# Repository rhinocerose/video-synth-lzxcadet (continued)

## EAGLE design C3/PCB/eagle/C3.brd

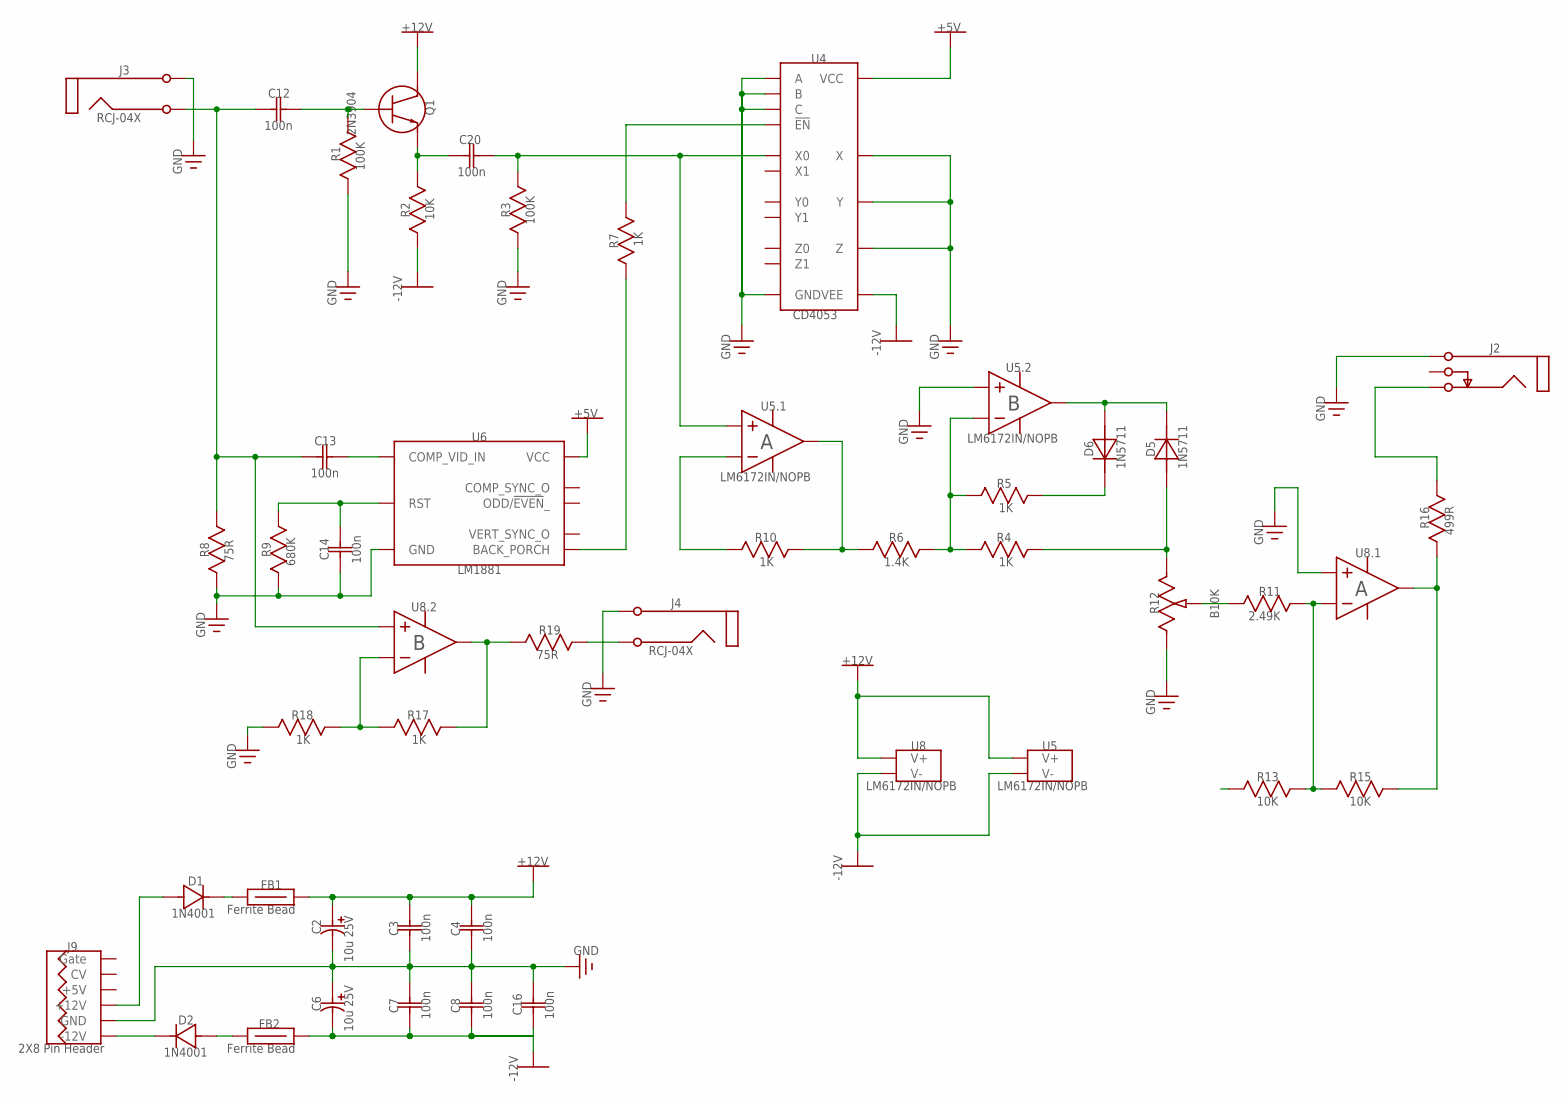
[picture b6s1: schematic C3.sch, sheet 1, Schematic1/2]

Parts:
C2, C6: 10u 25V; CAPPR-2/5.08
C3, C4, C7, C8, C12, C13, C14, C16, C20: 100n; CAP-2.54/6.6X3
D1, D2: 1N4001; DO-41
D5, D6: 1N5711; DO-35
FB1, FB2: 68R; FB-10.16/4.45X3.5
J2: PJ302M
J3: RCJ-04X
J4: RCJ-04X_23; RCJ-04X
J9: 2X8_PIN_HEADER; IDC16M
Q1: 2N3904; TO-92
R1, R3: 100K; RES-7.62/5.1X2.5
R2, R13, R15: 10K; RES-7.62/5.1X2.5
R4, R5, R7, R10, R17, R18: 1K; RES-7.62/5.1X2.5
R6: 1.4K; RES-7.62/5.1X2.5
R8, R19: 75R; RES-7.62/5.1X2.5
R9: 680K; RES-7.62/5.1X2.5
R11: 2.49K; RES-7.62/5.1X2.5
R12: B10K; ALPHA9H
R16: 499R; RES-7.62/5.1X2.5
U4: CD4053; DIP-16
U5, U8: LM6172IN/NOPB; DIP-8_16
U6: LM1881; DIP-8

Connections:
0V: C2.2 (MINUS), C3.2, C4.2, C6.1 (PLUS), C7.1, C8.1, C14.1, C16.1, J2.1A (Sleeve), J2.1B (Sleeve), J3.1 (Sleeve), J4.1 (Sleeve), J9.3 (GND), J9.4 (GND), J9.5 (GND), J9.6, J9.7, J9.8, R1.2 (B), R3.2 (B), R8.1 (A), R9.1 (A), R12.1 (CCW), R18.1 (A), U4.4 (Z), U4.8 (GND), U4.9 (C), U4.10 (B), U4.11 (A), U4.14 (X), U4.15 (Y), U5.5 (IN+), U6.4 (GND), U8.3 (IN+); also elsewhere on the board
+5V: U4.16 (VCC), U6.8 (VCC); also elsewhere on the board
+12V: C2.1 (PLUS), C3.1, C4.1, FB1.2, Q1.3 (C), U5.8 (V+), U8.8 (V+); also elsewhere on the board
-12V: C6.2 (MINUS), C7.2, C8.2, C16.2, FB2.2, R2.2 (B), U4.7 (VEE), U5.4 (V-), U8.4 (V-); also elsewhere on the board
BIAS_POT_OUT: R13.1 (A); also elsewhere on the board
Net_0: C20.2, Q1.1 (E), R2.1 (A)
Net_1: D2.2 (A), FB2.1
Net_2: D1.1 (K), FB1.1
Net_3: C20.1, R3.1 (A), U4.12 (X0), U5.3 (IN+)
Net_4: C13.2, U6.2 (COMP_VID_IN)
Net_5: D2.1 (K), J9.1 (-12V), J9.2 (-12V)
Net_6: R7.1 (A), U4.6 (!EN)
Net_7: R10.1 (A), U5.2 (IN-)
Net_8: J2.3A (Tip), J2.3B (Tip), R16.2 (B)
Net_9: R17.2 (B), R19.1 (A), U8.7 (OUT)
Net_10: R4.1 (A), R5.1 (A), R6.2 (B), U5.6 (IN-)
Net_11: D5.2 (A), R4.2 (B), R12.3 (CW)
Net_12: D6.1 (K), R5.2 (B)
Net_14: J9.11 (+5V), J9.12 (+5V)
Net_15: J9.13 (CV), J9.14 (CV)
Net_16: J9.15 (Gate), J9.16 (Gate)
Net_20: C12.1, Q1.2 (B), R1.1 (A)
Net_21: J2.2A (Switch), J2.2B (Switch)
Net_22: D5.1 (K), D6.2 (A), U5.7 (OUT)
Net_33: D1.2 (A), J9.9 (+12V), J9.10 (+12V)
Net_34: C12.2, C13.1, J3.2 (Tip), R8.2 (B), U8.5 (IN+)
Net_35: C14.2, R9.2 (B), U6.6 (RST)
Net_36: R7.2 (B), U6.5 (BACK_PORCH)
Net_37: R6.1 (A), R10.2 (B), U5.1 (OUT)
Net_38: R11.1 (A), R12.2 (W)
Net_39: R11.2 (B), R13.2 (B), R15.1 (A), U8.2 (IN-)
Net_40: R15.2 (B), R16.1 (A), U8.1 (OUT)
Net_42: R17.1 (A), R18.2 (B), U8.6 (IN-)
Net_43: J4.2 (Tip), R19.2 (B)

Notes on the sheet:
10u 25V
100n
C13
C14
1N4001
2N3904
RCJ-04X
100K
2X8 Pin Header
FB1
Ferrite Bead
FB2
C12
GND
+12V
-12V
+5V
75R
680K
LM1881
U5.1
LM6172IN/NOPB
10K
C20
CD4053
1N5711
1.4K
R12
B10K
U5.2
R10
U8.1
U8.2
R11
2.49K
R13
R15
R16
499R
R17

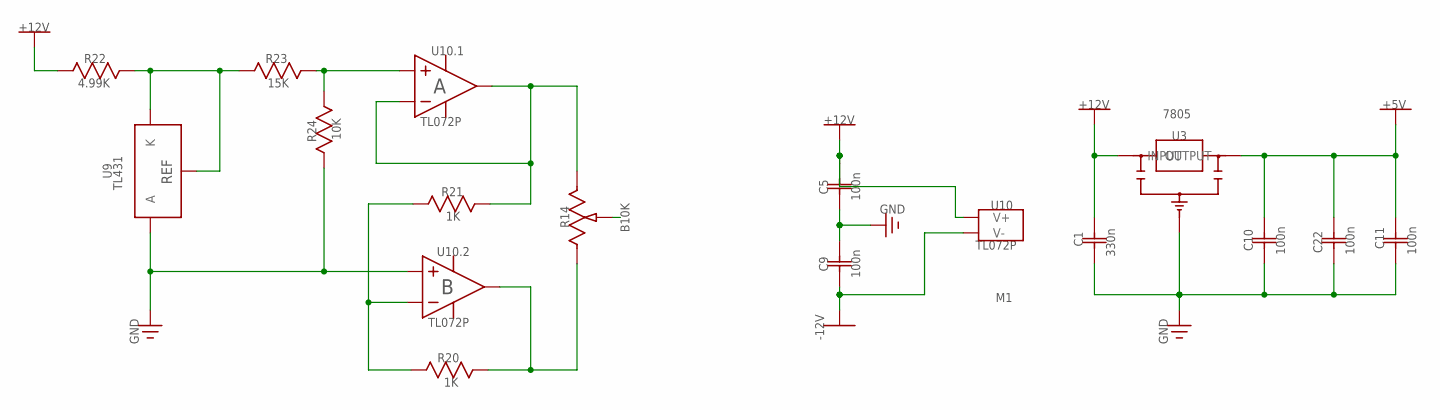
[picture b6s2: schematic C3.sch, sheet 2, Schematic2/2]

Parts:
C1: 330n; CAP-2.54/6.6X3
C5, C9, C10, C11, C22: 100n; CAP-2.54/6.6X3
M1: KEYSTONE621
R14: B10K; ALPHA9H
R20, R21: 1K; RES-7.62/5.1X2.5
R22: 4.99K; RES-7.62/5.1X2.5
R23: 15K; RES-7.62/5.1X2.5
R24: 10K; RES-7.62/5.1X2.5
U3: 7805; TO-220H
U9: TL431; TO-92-100R
U10: TL072P; DIP-8_16

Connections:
0V: C1.2, C5.2, C9.1, C10.2, C11.2, C22.2, R24.2 (B), U3.2 (GND), U9.2 (A), U10.5 (IN+); also elsewhere on the board
+5V: C10.1, C11.1, C22.1, U3.3 (OUTPUT); also elsewhere on the board
+12V: C1.1, C5.1, R22.2 (B), U3.1 (INPUT), U10.8 (V+); also elsewhere on the board
-12V: C9.2, U10.4 (V-); also elsewhere on the board
BIAS_POT_OUT: R14.2 (W); also elsewhere on the board
Net_13: R20.1 (A), R21.1 (A), U10.6 (IN-)
Net_17: R14.1 (CCW), R21.2 (B), U10.1 (OUT), U10.2 (IN-)
Net_18: R22.1 (A), R23.2 (B), U9.1 (K), U9.3 (REF)
Net_19: R14.3 (CW), R20.2 (B), U10.7 (OUT)
Net_30: R23.1 (A), R24.1 (A), U10.3 (IN+)

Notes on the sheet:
330n
C10
100n
C22
GND
+5V
7805
R14
B10K
+12V
R20
R21
R22
4.99K
R23
15K
R24
10K
REF
TL431
U10.1
TL072P
U10.2
U10
-12V
C11

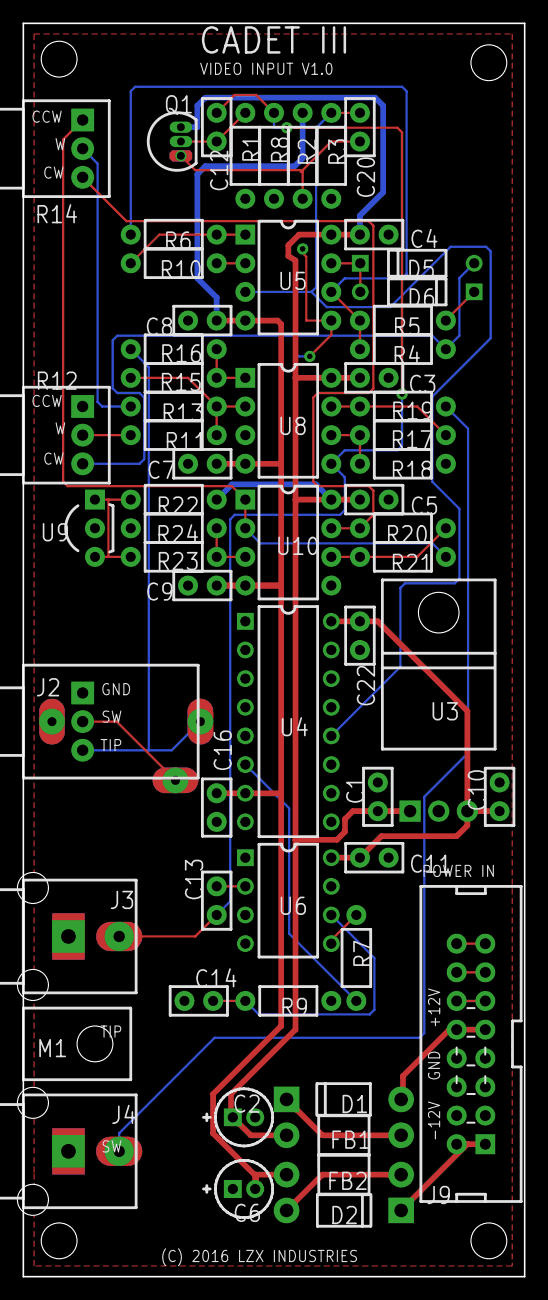
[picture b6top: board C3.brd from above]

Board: 2 copper layers, 44.5 x 111.1 mm, 60 parts (0 on the bottom side), 39 nets.

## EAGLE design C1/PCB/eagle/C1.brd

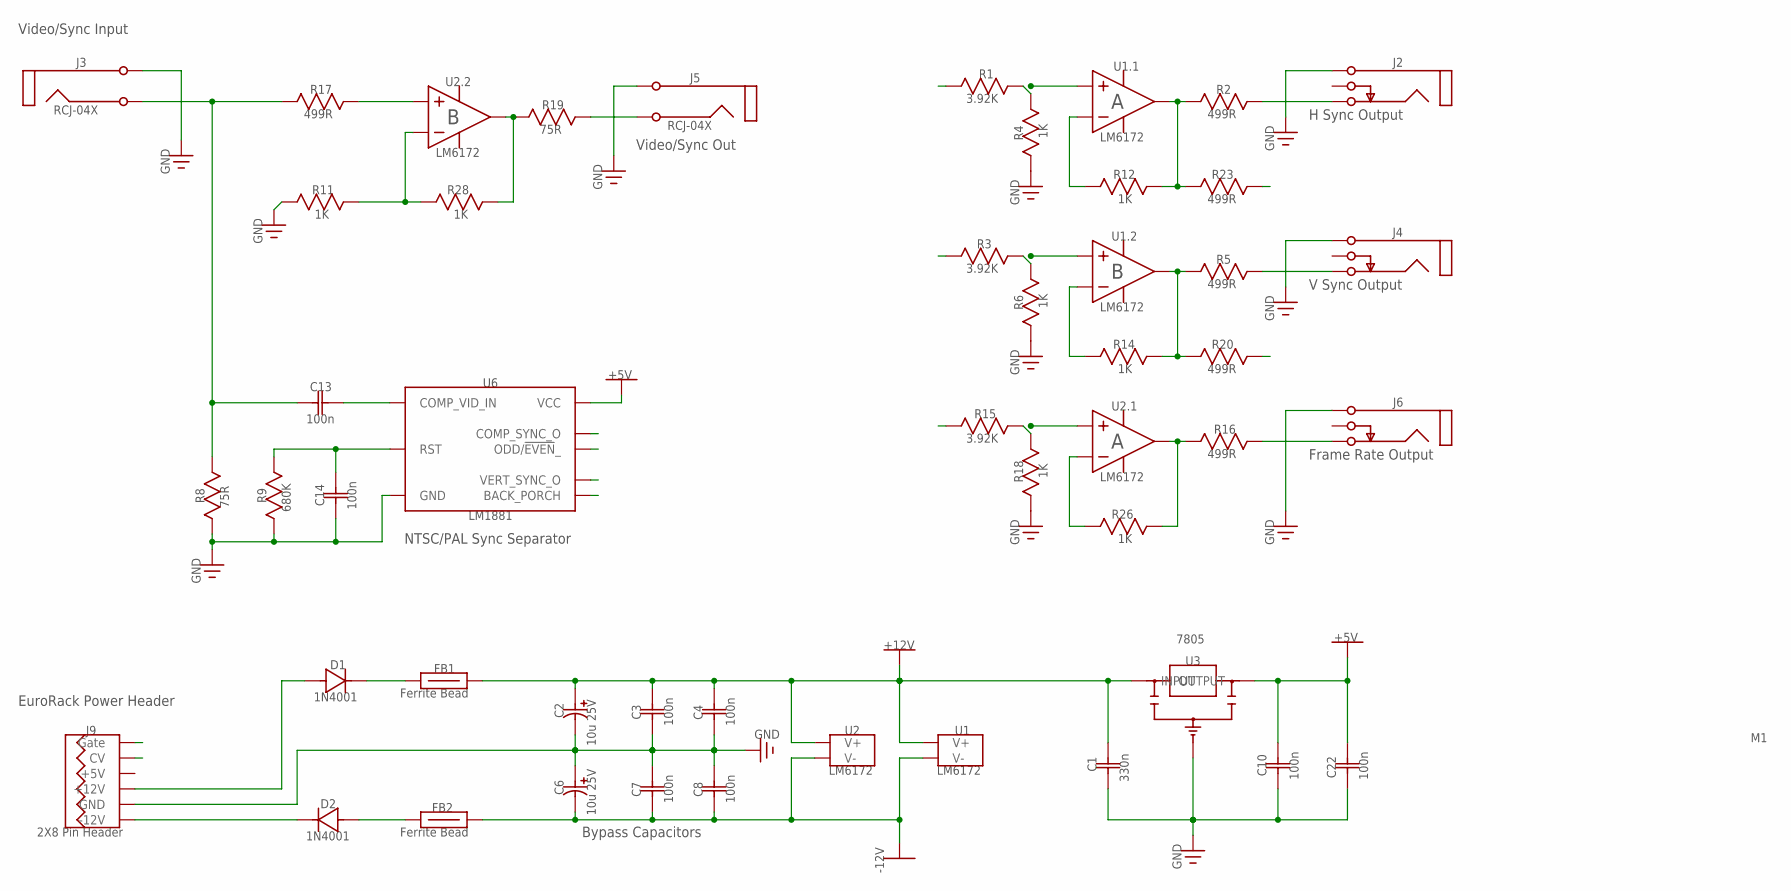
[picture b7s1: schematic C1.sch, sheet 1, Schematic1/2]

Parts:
C1: 330n; CAP-2.54/6.6X3
C2, C6: 10u 25V; CAPPR-2/5.08
C3, C4, C7, C8, C10, C13, C14, C22: 100n; CAP-2.54/6.6X3
D1, D2: 1N4001; DO-41
FB1, FB2: 68R; FB-10.16/4.45X3.5
J2, J4, J6: 3.5MM_JACK; PJ302M
J3: RCJ-04X
J5: RCJ-04X_23; RCJ-04X
J9: 2X8_PIN_HEADER; IDC16M
M1: KEYSTONE621
R1, R3, R15: 3.92K; RES-7.62/5.1X2.5
R2, R5, R16, R17, R20, R23: 499R; RES-7.62/5.1X2.5
R4, R6, R11, R12, R14, R18, R26, R28: 1K; RES-7.62/5.1X2.5
R8, R19: 75R; RES-7.62/5.1X2.5
R9: 680K; RES-7.62/5.1X2.5
U1, U2: LM6172; DIP-8
U3: 7805; TO-220H
U6: LM1881; DIP-8_12

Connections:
0V: C1.2, C2.2 (MINUS), C3.2, C4.2, C6.1 (PLUS), C7.1, C8.1, C10.2, C14.1, C22.2, J2.1A (Sleeve), J2.1B (Sleeve), J3.1 (Sleeve), J4.1A (Sleeve), J4.1B (Sleeve), J5.1 (Sleeve), J6.1A (Sleeve), J6.1B (Sleeve), J9.3 (GND), J9.4 (GND), J9.5 (GND), J9.6, J9.7, J9.8, R4.1 (A), R6.1 (A), R8.1 (A), R9.1 (A), R11.1 (A), R18.1 (A), U3.2 (GND), U6.4 (GND); also elsewhere on the board
+5V: C10.1, C22.1, U3.3 (OUTPUT), U6.8 (VCC); also elsewhere on the board
+12V: C1.1, C2.1 (PLUS), C3.1, C4.1, FB1.2, U1.8 (V+), U2.8 (V+), U3.1 (INPUT)
-12V: C6.2 (MINUS), C7.2, C8.2, FB2.2, U1.4 (V-), U2.4 (V-)
ATMEGA88_HSYNC_INV: R1.1 (A); also elsewhere on the board
ATMEGA88_ODDEVEN: R15.1 (A); also elsewhere on the board
ATMEGA88_VSYNC_INV: R3.1 (A); also elsewhere on the board
HSYNC_BUS_OUT: J9.13 (CV), J9.14 (CV), R23.2 (B)
LM1881_CSYNC: U6.1 (COMP_SYNC_O); also elsewhere on the board
LM1881_ODDEVEN: U6.7 (ODD/!EVEN!_); also elsewhere on the board
LM1881_VSYNC: U6.3 (VERT_SYNC_O); also elsewhere on the board
Net_0: J5.2 (Tip), R19.2 (B)
Net_1: D2.2 (A), FB2.1
Net_2: D1.1 (K), FB1.1
Net_3: R14.1 (A), U1.6 (IN-)
Net_4: C13.2, U6.2 (COMP_VID_IN)
Net_5: D2.1 (K), J9.1 (-12V), J9.2 (-12V)
Net_6: R3.2 (B), R6.2 (B), U1.5 (IN+)
Net_7: J4.3A (Tip), J4.3B (Tip), R5.2 (B)
Net_8: J2.2A (Switch), J2.2B (Switch)
Net_9: R1.2 (B), R4.2 (B), U1.3 (IN+)
Net_10: J9.11 (+5V), J9.12 (+5V)
Net_11: J2.3A (Tip), J2.3B (Tip), R2.2 (B)
Net_12: R5.1 (A), R14.2 (B), R20.1 (A), U1.7 (OUT)
Net_14: R11.2 (B), R28.1 (A), U2.6 (IN-)
Net_19: R15.2 (B), R18.2 (B), U2.3 (IN+)
Net_20: J6.3A (Tip), J6.3B (Tip), R16.2 (B)
Net_21: R26.1 (A), U2.2 (IN-)
Net_22: R16.1 (A), R26.2 (B), U2.1 (OUT)
Net_24: R17.2 (B), U2.5 (IN+)
Net_27: R19.1 (A), R28.2 (B), U2.7 (OUT)
Net_33: D1.2 (A), J9.9 (+12V), J9.10 (+12V)
Net_34: C13.1, J3.2 (Tip), R8.2 (B), R17.1 (A)
Net_35: C14.2, R9.2 (B), U6.6 (RST)
Net_52: R12.1 (A), U1.2 (IN-)
Net_53: R2.1 (A), R12.2 (B), R23.1 (A), U1.1 (OUT)
Net_60: J4.2A (Switch), J4.2B (Switch)
Net_61: J6.2A (Switch), J6.2B (Switch)
VSYNC_BUS_OUT: J9.15 (Gate), J9.16 (Gate), R20.2 (B)

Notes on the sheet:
EuroRack Power Header
H Sync Output
V Sync Output
Frame Rate Output
NTSC/PAL Sync Separator
Bypass Capacitors
Video/Sync Out
Video/Sync Input
330n
10u 25V
100n
C10
C13
C14
C22
1N4001
RCJ-04X
2X8 Pin Header
FB1
Ferrite Bead
FB2
GND
+12V
-12V
+5V
3.92K
499R
75R
680K
R11
R12
R14
R15
R16
R17
R18
R19
R20
R23
R26

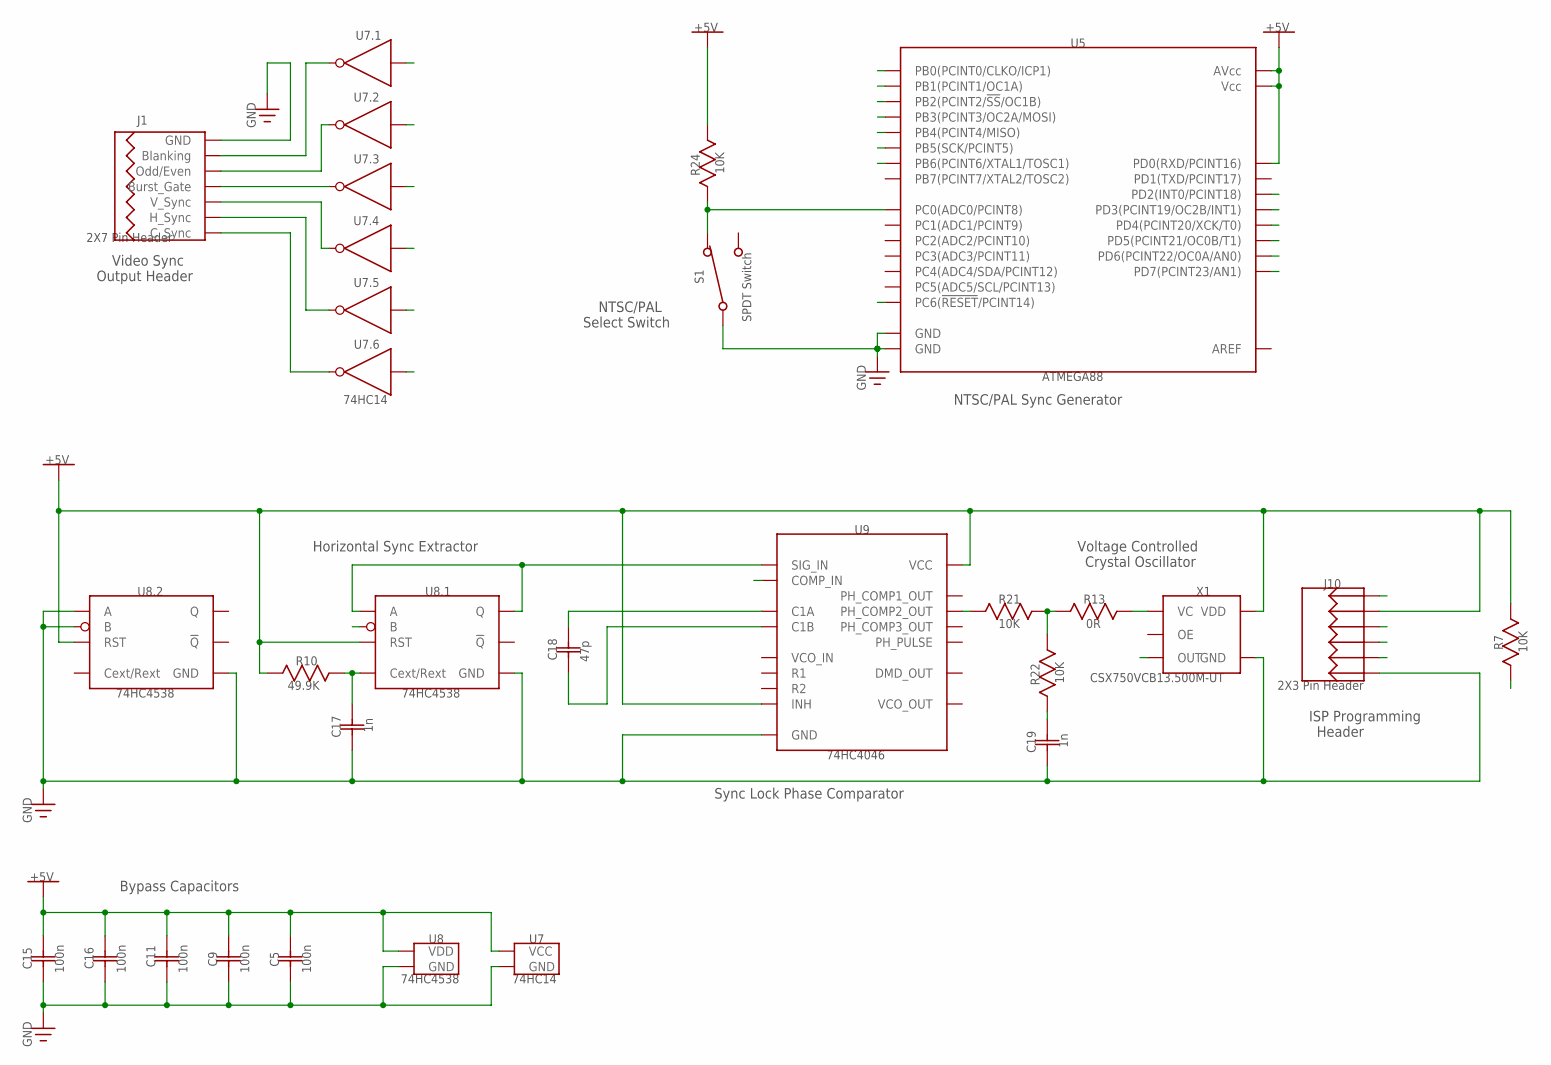
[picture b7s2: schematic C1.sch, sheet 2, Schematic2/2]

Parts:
C5, C9, C11, C15, C16: 100n; CAP-2.54/6.6X3
C17, C19: 1n; CAP-2.54/6.6X3
C18: 47p; CAP-2.54/6.6X3
J1: 2X7_PIN_HEADER; IDC14M
J10: 2X3_PIN_HEADER; HDR-2X3T/2.54X2.54/8X5
R7, R21, R22, R24: 10K; RES-7.62/5.1X2.5
R10: 49.9K; RES-7.62/5.1X2.5
R13: 0R; RES-7.62/5.1X2.5
S1: SPDT_SWITCH; 10TF230-DIY
U5: ATMEGA88; DIP-28
U7: 74HC14; DIP-14
U8: 74HC4538; DIP-16
U9: 74HC4046; DIP-16
X1: CSX750VCB13.500M-UT; CSX-750V

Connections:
0V: C5.2, C9.2, C11.2, C15.2, C16.2, C17.2, C19.2, J1.1 (GND), J1.2 (GND), J10.6, S1.2 (C1), S1.2B (C1), U5.8 (GND), U5.22 (GND), U7.7 (GND), U8.1 (GND), U8.8 (GND), U8.11 (B), U8.12 (A), U8.15 (GND), U9.8 (GND), X1.3 (GND); also elsewhere on the board
+5V: C5.1, C9.1, C11.1, C15.1, C16.1, J10.2, R7.2 (B), R10.2 (B), R24.1 (A), U5.2 (PD0(RXD/PCINT16)), U5.7 (Vcc), U5.20 (AVcc), U7.14 (VCC), U8.3 (RST), U8.13 (RST), U8.16 (VDD), U9.5 (INH), U9.16 (VCC), X1.6 (VDD); also elsewhere on the board
ATMEGA88_BLANKING_INV: U5.11 (PD5(PCINT21/OC0B/T1)), U7.1 (A)
ATMEGA88_BURSTGATE_INV: U5.5 (PD3(PCINT19/OC2B/INT1)), U7.5 (A)
ATMEGA88_CSYNC_INV: U5.16 (PB2(PCINT2/!SS!/OC1B)), U7.13 (A)
ATMEGA88_HSYNC_INV: U5.15 (PB1(PCINT1/OC1A)), U7.11 (A), U9.3 (COMP_IN); also elsewhere on the board
ATMEGA88_MISO: J10.1, U5.18 (PB4(PCINT4/MISO))
ATMEGA88_MOSI: J10.4, U5.17 (PB3(PCINT3/OC2A/MOSI))
ATMEGA88_ODDEVEN: U5.12 (PD6(PCINT22/OC0A/AN0)); also elsewhere on the board
ATMEGA88_ODDEVEN_INV: U5.14 (PB0(PCINT0/CLKO/ICP1)), U7.3 (A)
ATMEGA88_RESET: J10.5, R7.1 (A), U5.1 (PC6(!RESET!/PCINT14))
ATMEGA88_SCK: J10.3, U5.19 (PB5(SCK/PCINT5))
ATMEGA88_VSYNC_INV: U5.13 (PD7(PCINT23/AN1)), U7.9 (A); also elsewhere on the board
CLOCK_OUT: U5.9 (PB6(PCINT6/XTAL1/TOSC1)), X1.4 (OUT)
LM1881_CSYNC: U8.5 (B); also elsewhere on the board
LM1881_ODDEVEN: U5.6 (PD4(PCINT20/XCK/T0)); also elsewhere on the board
LM1881_VSYNC: U5.4 (PD2(INT0/PCINT18)); also elsewhere on the board
Net_15: J1.3 (Blanking), J1.4 (Blanking), U7.2 (Y)
Net_16: J1.5 (Odd/Even), J1.6 (Odd/Even), U7.4 (Y)
Net_40: U8.4 (A), U8.6 (Q), U9.14 (SIG_IN)
Net_41: C17.1, R10.1 (A), U8.2 (Cext/Rext)
Net_42: C18.1, U9.6 (C1A)
Net_43: C18.2, U9.7 (C1B)
Net_44: C19.1, R22.2 (B)
Net_45: R13.2 (B), R21.2 (B), R22.1 (A)
Net_46: R21.1 (A), U9.13 (PH_COMP2_OUT)
Net_47: J1.7 (Burst_Gate), J1.8 (Burst_Gate), U7.6 (Y)
Net_48: J1.9 (V_Sync), J1.10 (V_Sync), U7.8 (Y)
Net_49: J1.11 (H_Sync), J1.12 (H_Sync), U7.10 (Y)
Net_50: J1.13 (C_Sync), J1.14 (C_Sync), U7.12 (Y)
Net_58: R13.1 (A), X1.1 (VC)
Net_62: R24.2 (B), S1.1 (C3), S1.1B (C3), U5.23 (PC0(ADC0/PCINT8))
Net_63: S1.3 (C2), S1.3B (C2)

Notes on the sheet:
Sync Lock Phase Comparator
Horizontal Sync Extractor
NTSC/PAL Sync Generator
ISP Programming
Video Sync
Output Header
Header
Bypass Capacitors
Voltage Controlled
Crystal Oscillator
NTSC/PAL
Select Switch
100n
C11
C15
C16
C17
C18
47p
C19
2X7 Pin Header
J10
2X3 Pin Header
GND
+5V
10K
R10
49.9K
R21
R22
R24
ATMEGA88
U7.1
U7.2
U7.3
U7.4
U7.5
U7.6
74HC14
U8.1

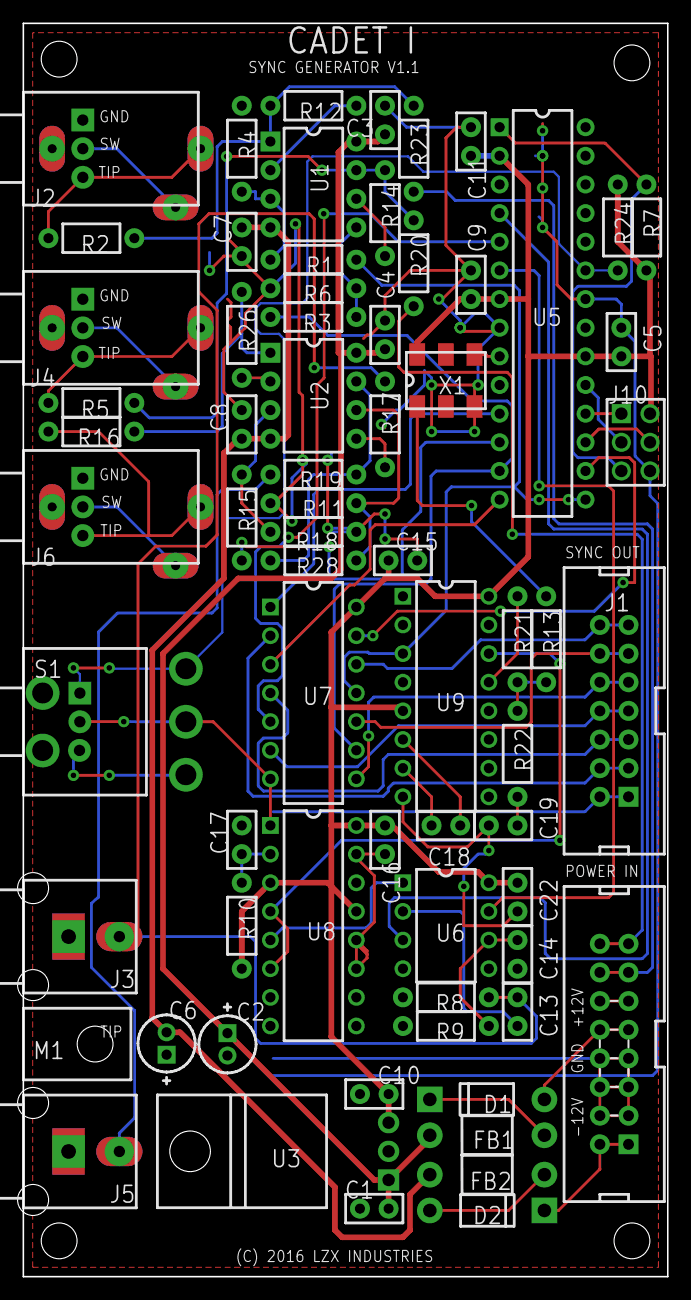
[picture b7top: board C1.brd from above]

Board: 2 copper layers, 57.1 x 111.1 mm, 68 parts (0 on the bottom side), 64 nets.

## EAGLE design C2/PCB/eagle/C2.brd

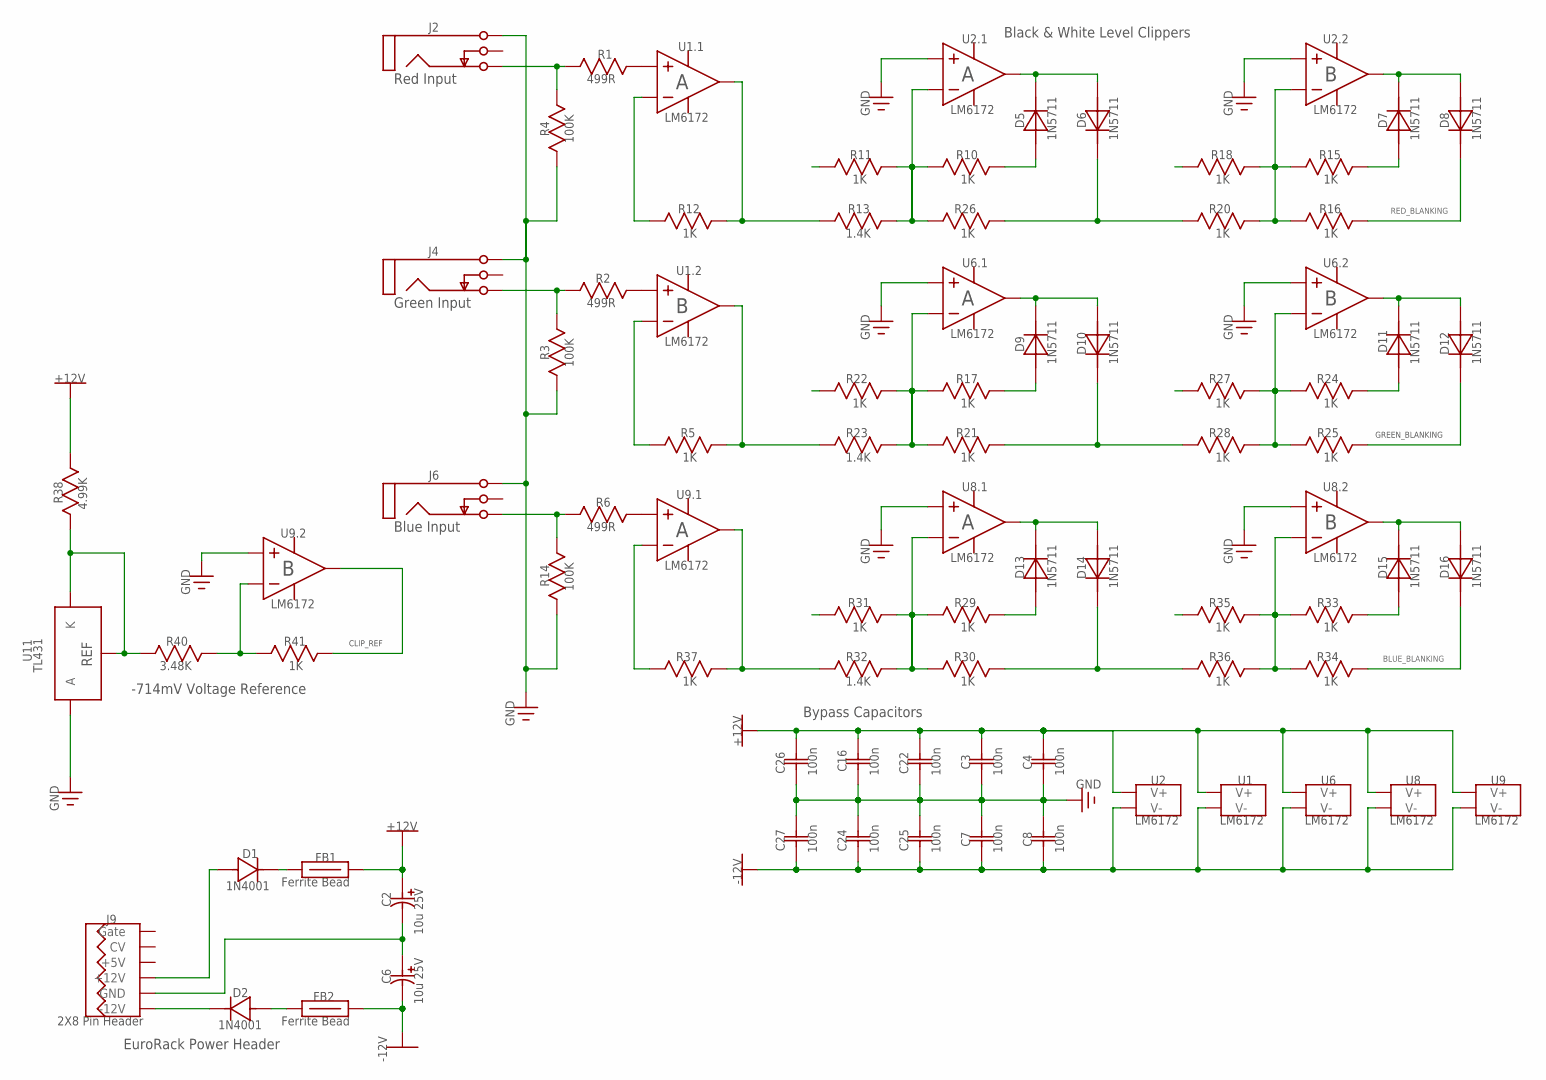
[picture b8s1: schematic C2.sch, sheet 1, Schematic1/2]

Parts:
C2, C6: 10u 25V; CAPPR-2/5.08
C3, C4, C7, C8, C16, C22, C24, C25, C26, C27: 100n; CAP-2.54/6.6X3
D1, D2: 1N4001; DO-41
D5, D6, D7, D8, D9, D10, D11, D12, D13, D14, D15, D16: 1N5711; DO-35
FB1, FB2: 68R; FB-10.16/4.45X3.5
J2, J4, J6: 3.5MM_JACK; PJ302M
J9: 2X8_PIN_HEADER; IDC16M
R1, R2, R6: 499R; RES-7.62/5.1X2.5
R3, R4, R14: 100K; RES-7.62/5.1X2.5
R5, R10, R11, R12, R15, R16, R17, R18, R20, R21, R22, R24, R25, R26, R27, R28, R29, R30, R31, R33, R34, R35, R36, R37, R41: 1K; RES-7.62/5.1X2.5
R13, R23, R32: 1.4K; RES-7.62/5.1X2.5
R38: 4.99K; RES-7.62/5.1X2.5
R40: 3.48K; RES-7.62/5.1X2.5
U1, U2, U6, U8, U9: LM6172; DIP-8
U11: TL431; TO-92-100R

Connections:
0V: C2.2 (MINUS), C6.1 (PLUS), J9.3 (GND), J9.4 (GND), J9.5 (GND), J9.6, J9.7, J9.8
+12V: C2.1 (PLUS), C3.1, C4.1, C16.1, C22.1, C26.1, FB1.2, R38.2 (B), U1.8 (V+), U2.8 (V+), U6.8 (V+), U8.8 (V+), U9.8 (V+); also elsewhere on the board
-12V: C6.2 (MINUS), C7.2, C8.2, C24.2, C25.2, C27.2, FB2.2, U1.4 (V-), U2.4 (V-), U6.4 (V-), U8.4 (V-), U9.4 (V-); also elsewhere on the board
BLUE_BLANKING: D16.1 (K), R34.2 (B); also elsewhere on the board
CLIP_REF: R11.1 (A), R18.1 (A), R22.1 (A), R27.1 (A), R31.1 (A), R35.1 (A), R41.2 (B), U9.7 (OUT)
GREEN_BLANKING: D12.1 (K), R25.2 (B); also elsewhere on the board
Net_1: D2.2 (A), FB2.1
Net_2: D1.1 (K), FB1.1
Net_3: R5.1 (A), U1.6 (IN-)
Net_5: D2.1 (K), J9.1 (-12V), J9.2 (-12V)
Net_6: J4.3A (Tip), J4.3B (Tip), R2.1 (A), R3.2 (B)
Net_9: J2.3A (Tip), J2.3B (Tip), R1.1 (A), R4.2 (B)
Net_12: R2.2 (B), U1.5 (IN+)
Net_13: R12.2 (B), R13.1 (A), U1.1 (OUT)
Net_14: R24.1 (A), R25.1 (A), R27.2 (B), R28.2 (B), U6.6 (IN-)
Net_16: R15.1 (A), R16.1 (A), R18.2 (B), R20.2 (B), U2.6 (IN-)
Net_17: D7.1 (K), D8.2 (A), U2.7 (OUT)
Net_19: D7.2 (A), R15.2 (B)
Net_20: D11.1 (K), D12.2 (A), U6.7 (OUT)
Net_21: R10.1 (A), R11.2 (B), R13.2 (B), R26.1 (A), U2.2 (IN-)
Net_22: D5.1 (K), D6.2 (A), U2.1 (OUT)
Net_23: D11.2 (A), R24.2 (B)
Net_24: R17.1 (A), R21.1 (A), R22.2 (B), R23.2 (B), U6.2 (IN-)
Net_25: D9.1 (K), D10.2 (A), U6.1 (OUT)
Net_26: D9.2 (A), R17.2 (B)
Net_27: D10.1 (K), R21.2 (B), R28.1 (A)
Net_29: R33.1 (A), R34.1 (A), R35.2 (B), R36.2 (B), U8.6 (IN-)
Net_30: D15.1 (K), D16.2 (A), U8.7 (OUT)
Net_31: D15.2 (A), R33.2 (B)
Net_32: R29.1 (A), R30.1 (A), R31.2 (B), R32.2 (B), U8.2 (IN-)
Net_33: D1.2 (A), J9.9 (+12V), J9.10 (+12V)
Net_34: D13.1 (K), D14.2 (A), U8.1 (OUT)
Net_36: D13.2 (A), R29.2 (B)
Net_45: D5.2 (A), R10.2 (B)
Net_46: D6.1 (K), R20.1 (A), R26.2 (B)
Net_49: D14.1 (K), R30.2 (B), R36.1 (A)
Net_50: R1.2 (B), U1.3 (IN+)
Net_52: R12.1 (A), U1.2 (IN-)
Net_53: C3.2, C4.2, C7.1, C8.1, C16.2, C22.2, C24.1, C25.1, C26.2, C27.1, J2.1A (Sleeve), J2.1B (Sleeve), J4.1A (Sleeve), J4.1B (Sleeve), J6.1A (Sleeve), J6.1B (Sleeve), R3.1 (A), R4.1 (A), R14.1 (A), U2.3 (IN+), U2.5 (IN+), U6.3 (IN+), U6.5 (IN+), U8.3 (IN+), U8.5 (IN+), U9.5 (IN+), U11.2 (A); also elsewhere on the board
Net_54: J6.3A (Tip), J6.3B (Tip), R6.1 (A), R14.2 (B)
Net_61: R5.2 (B), R23.1 (A), U1.7 (OUT)
Net_62: R6.2 (B), U9.3 (IN+)
Net_64: R37.1 (A), U9.2 (IN-)
Net_65: R32.1 (A), R37.2 (B), U9.1 (OUT)
Net_67: R38.1 (A), R40.1 (A), U11.1 (K), U11.3 (REF)
Net_68: R40.2 (B), R41.1 (A), U9.6 (IN-)
Net_76: J2.2A (Switch), J2.2B (Switch)
Net_77: J4.2A (Switch), J4.2B (Switch)
Net_78: J6.2A (Switch), J6.2B (Switch)
Net_79: J9.11 (+5V), J9.12 (+5V)
Net_80: J9.13 (CV), J9.14 (CV)
Net_81: J9.15 (Gate), J9.16 (Gate)
RED_BLANKING: D8.1 (K), R16.2 (B); also elsewhere on the board

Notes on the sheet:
EuroRack Power Header
Bypass Capacitors
GREEN_BLANKING
Black & White Level Clippers
Red Input
Green Input
Blue Input
CLIP_REF
-714mV Voltage Reference
10u 25V
100n
1N4001
2X8 Pin Header
FB1
Ferrite Bead
FB2
U9.1
LM6172
U9.2
GND
+12V
-12V
499R
C16
100K
R12
R10
R26
R17
U1.1
U1.2
U2.1
U2.2
1N5711
R11
R13
1.4K
R15
R16
R21

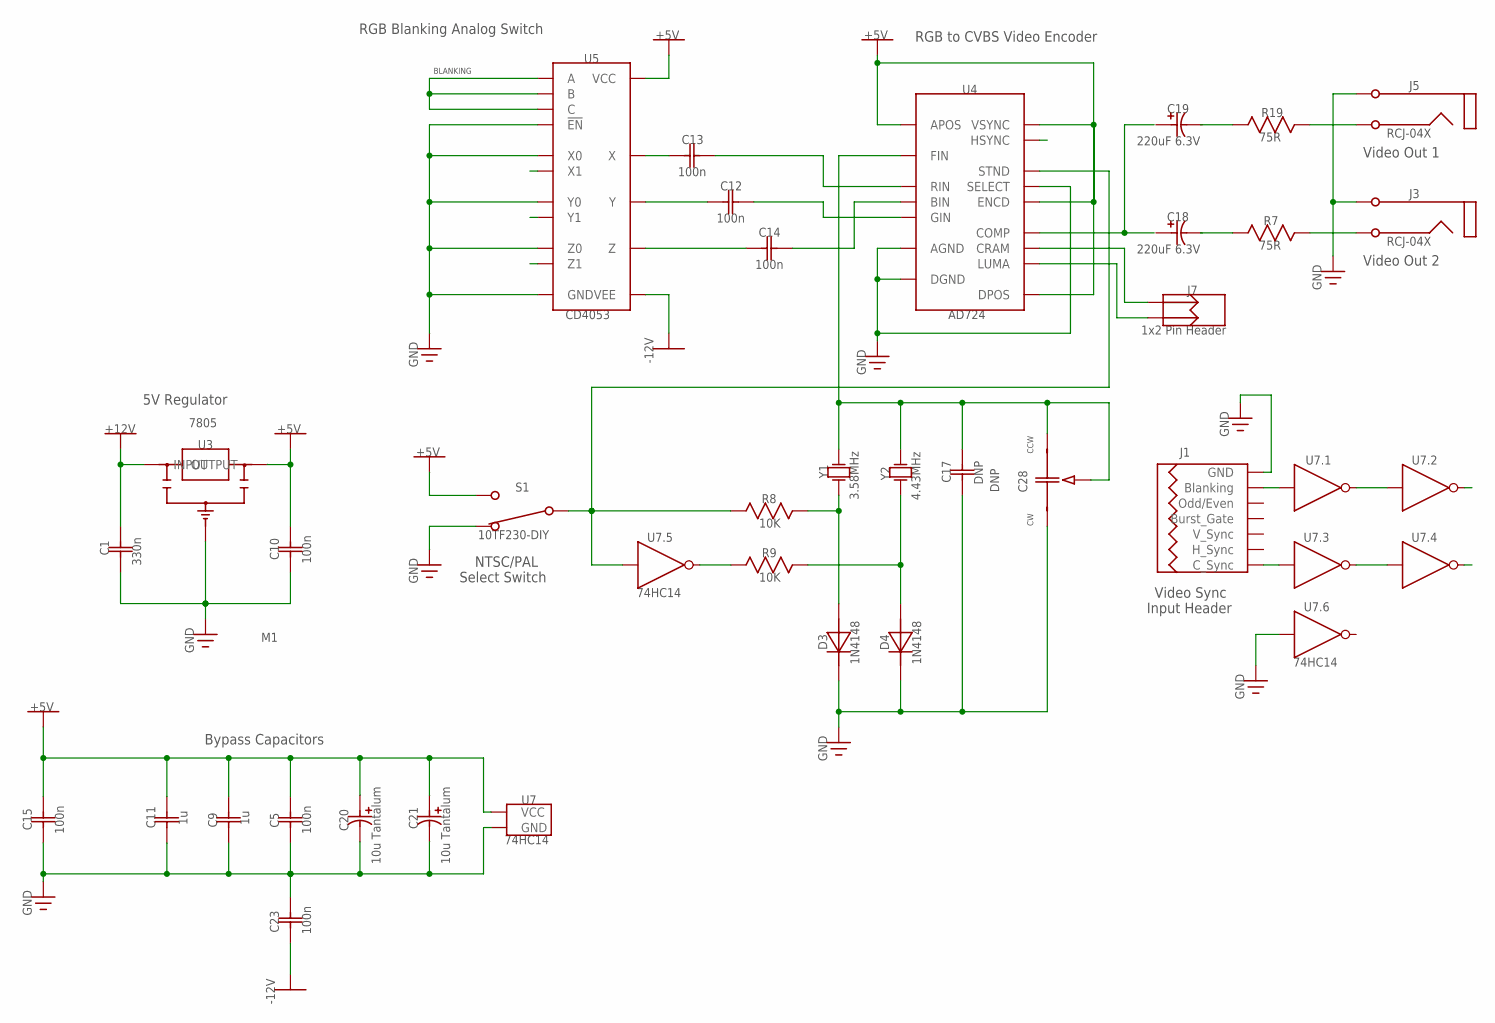
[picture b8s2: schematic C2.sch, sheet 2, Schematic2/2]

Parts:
C1: 330n; CAP-2.54/6.6X3
C5, C10, C12, C13, C14, C15, C23: 100n; CAP-2.54/6.6X3
C9, C11: 1u; CAP-2.54/6.6X3
C17: DNP; CAP-2.54/6.6X3
C18, C19: 220uF 6.3V; CAPPR-2/5.08
C20, C21: 10u Tantalum; PCAP-2.54/6.6X3
C28: DNP; GYA22000
D3, D4: 1N4148; DO-35
J1: LZXSYNC14; IDC14M
J3, J5: RCJ-04X
J7: 1X2_PIN_HEADER; HDR-2X1T/2.54X2.54/3X5
M1: KEYSTONE621
R7, R19: 75R; RES-7.62/5.1X2.5
R8, R9: 10K; RES-7.62/5.1X2.5
S1: 10TF230-DIY
U3: 7805; TO-220H
U4: AD724; SOIC-16/300MIL
U5: CD4053; DIP-16
U7: 74HC14; DIP-14
Y1: 3.58MHz; HC-49U
Y2: 4.43MHz; HC-49U

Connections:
+5V: C5.1, C9.1, C10.1, C11.1, C15.1, C20.1 (PLUS), C21.1 (PLUS), S1.3 (C2), S1.3B (C2), U3.3 (OUTPUT), U4.4 (APOS), U4.5 (ENCD), U4.14 (DPOS), U4.15 (VSYNC), U5.16 (VCC), U7.14 (VCC)
+12V: C1.1, U3.1 (INPUT); also elsewhere on the board
-12V: C23.2, U5.7 (VEE); also elsewhere on the board
BLANKING: U5.9 (C), U5.10 (B), U5.11 (A), U7.4 (Y)
BLUE_BLANKING: U5.3 (Z1); also elsewhere on the board
CSYNC: U4.16 (HSYNC), U7.8 (Y)
GREEN_BLANKING: U5.1 (Y1); also elsewhere on the board
Net_0: J5.2 (Tip), R19.2 (B)
Net_4: J1.13 (C_Sync), J1.14 (C_Sync), U7.5 (A)
Net_7: C12.2, U4.7 (GIN)
Net_8: U7.6 (Y), U7.9 (A)
Net_10: C18.1 (PLUS), C19.1 (PLUS), U4.10 (COMP)
Net_11: C14.1, U5.4 (Z)
Net_15: C14.2, U4.8 (BIN)
Net_18: C13.2, U4.6 (RIN)
Net_28: J3.2 (Tip), R7.2 (B)
Net_35: D3.2 (A), R8.1 (A), Y1.1 (OSC1)
Net_37: D4.2 (A), R9.1 (A), Y2.1 (OSC1)
Net_38: C17.1, C28.CCW, C28.W, U4.3 (FIN), Y1.2 (OSC2), Y2.2 (OSC2)
Net_39: R8.2 (B), S1.2 (C1), S1.2B (C1), U4.1 (STND), U7.11 (A)
Net_40: R9.2 (B), U7.10 (Y)
Net_41: C12.1, U5.15 (Y)
Net_42: C13.1, U5.14 (X)
Net_43: C19.2 (MINUS), R19.1 (A)
Net_44: C18.2 (MINUS), R7.1 (A)
Net_47: J1.3 (Blanking), J1.4 (Blanking), U7.1 (A)
Net_48: U7.2 (Y), U7.3 (A)
Net_53: C1.2, C5.2, C9.2, C10.2, C11.2, C15.2, C17.2, C20.2 (MINUS), C21.2 (MINUS), C23.1, C28.CW, D3.1 (K), D4.1 (K), J1.1 (GND), J1.2 (GND), J3.1 (Sleeve), J5.1 (Sleeve), S1.1 (C3), S1.1B (C3), U3.2 (GND), U4.2 (AGND), U4.12 (SELECT), U4.13 (DGND), U5.2 (Y0), U5.5 (Z0), U5.6 (!EN), U5.8 (GND), U5.12 (X0), U7.7 (GND), U7.13 (A); also elsewhere on the board
Net_70: J7.1, U4.9 (CRAM)
Net_71: J7.2, U4.11 (LUMA)
Net_72: J1.7 (Burst_Gate), J1.8 (Burst_Gate)
Net_73: J1.9 (V_Sync), J1.10 (V_Sync)
Net_74: J1.11 (H_Sync), J1.12 (H_Sync)
Net_75: J1.5 (Odd/Even), J1.6 (Odd/Even)
RED_BLANKING: U5.13 (X1); also elsewhere on the board

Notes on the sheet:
5V Regulator
Video Sync
Input Header
Bypass Capacitors
Video Out 1
NTSC/PAL
Select Switch
Video Out 2
BLANKING
RGB to CVBS Video Encoder
RGB Blanking Analog Switch
330n
100n
C10
C11
GND
C15
RCJ-04X
AD724
+5V
C23
R19
75R
-12V
7805
U7.1
U7.2
U7.3
U7.4
U7.5
74HC14
U7.6
10TF230-DIY
C12
C13
C14
3.58MHz
4.43MHz
1N4148
C17

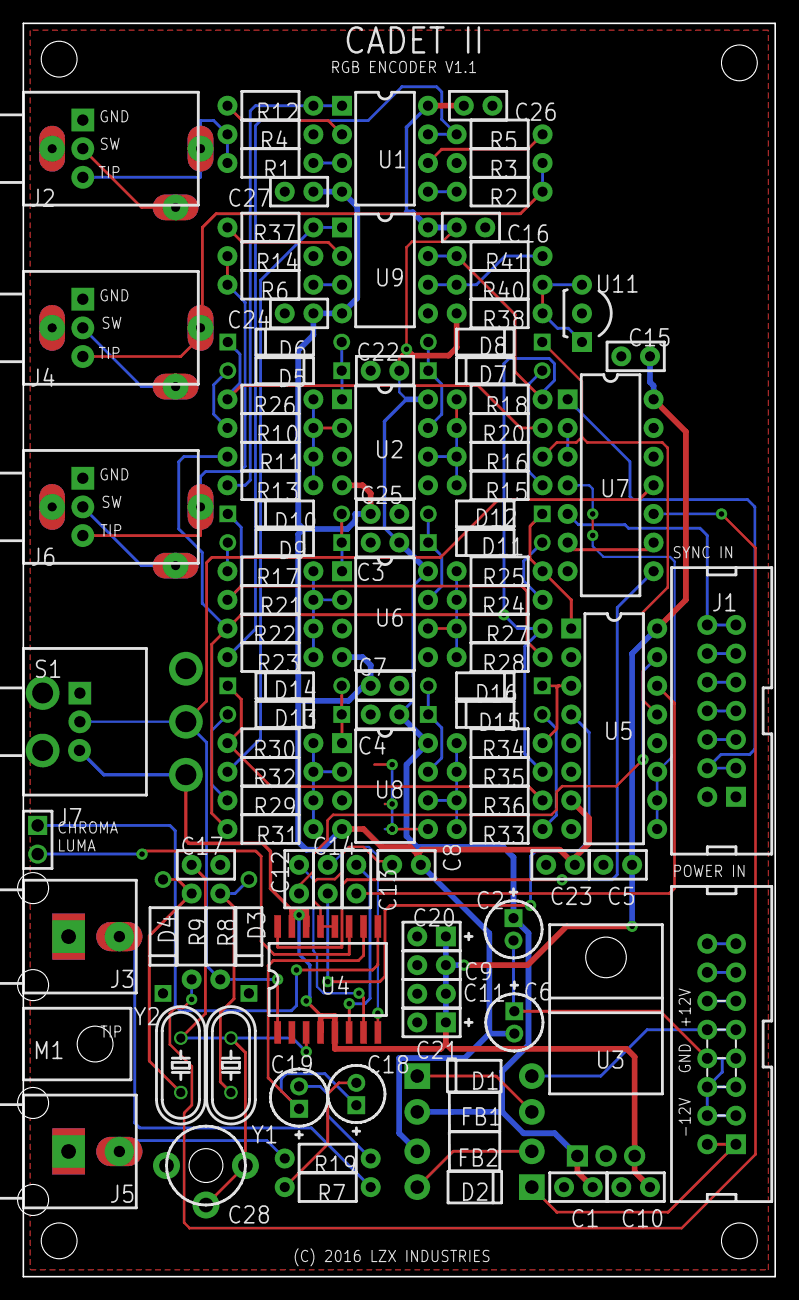
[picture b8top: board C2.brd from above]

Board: 2 copper layers, 66.7 x 111.1 mm, 108 parts (0 on the bottom side), 82 nets.

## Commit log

2025-08-17 Started converting to Eagle
2025-08-18 Done through C5
2025-08-18 All converted to Eagle
2025-08-25 Started work on C2
